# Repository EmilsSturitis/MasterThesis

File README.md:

# MasterThesis
repo with all of the source files

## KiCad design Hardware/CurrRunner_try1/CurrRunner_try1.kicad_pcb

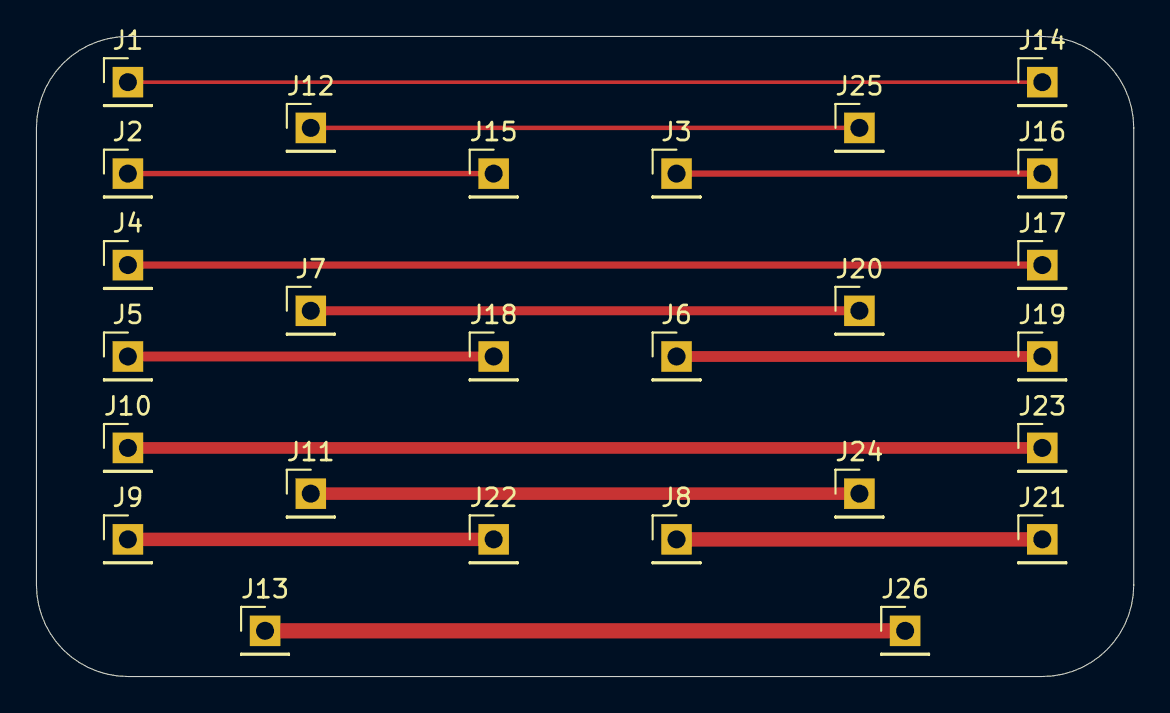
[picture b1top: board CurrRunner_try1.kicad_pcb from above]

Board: 2 copper layers, 61.0 x 35.6 mm, 26 parts (0 on the bottom side), 13 nets.

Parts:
J1, J2, J3, J4, J5, J6, J7, J8, J9, J10, J11, J12, J13, J14, J15, J16, J17, J18, J19, J20, J21, J22, J23, J24, J25, J26: Conn_01x01; PinHeader_1x01_P2.54mm_Vertical

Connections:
unnamed: J1.1, J14.1
unnamed: J10.1, J23.1
unnamed: J11.1, J24.1
unnamed: J12.1, J25.1
unnamed: J13.1, J26.1
unnamed: J2.1, J15.1
unnamed: J3.1, J16.1
unnamed: J4.1, J17.1
unnamed: J5.1, J18.1
unnamed: J6.1, J19.1
unnamed: J7.1, J20.1
unnamed: J8.1, J21.1
unnamed: J9.1, J22.1

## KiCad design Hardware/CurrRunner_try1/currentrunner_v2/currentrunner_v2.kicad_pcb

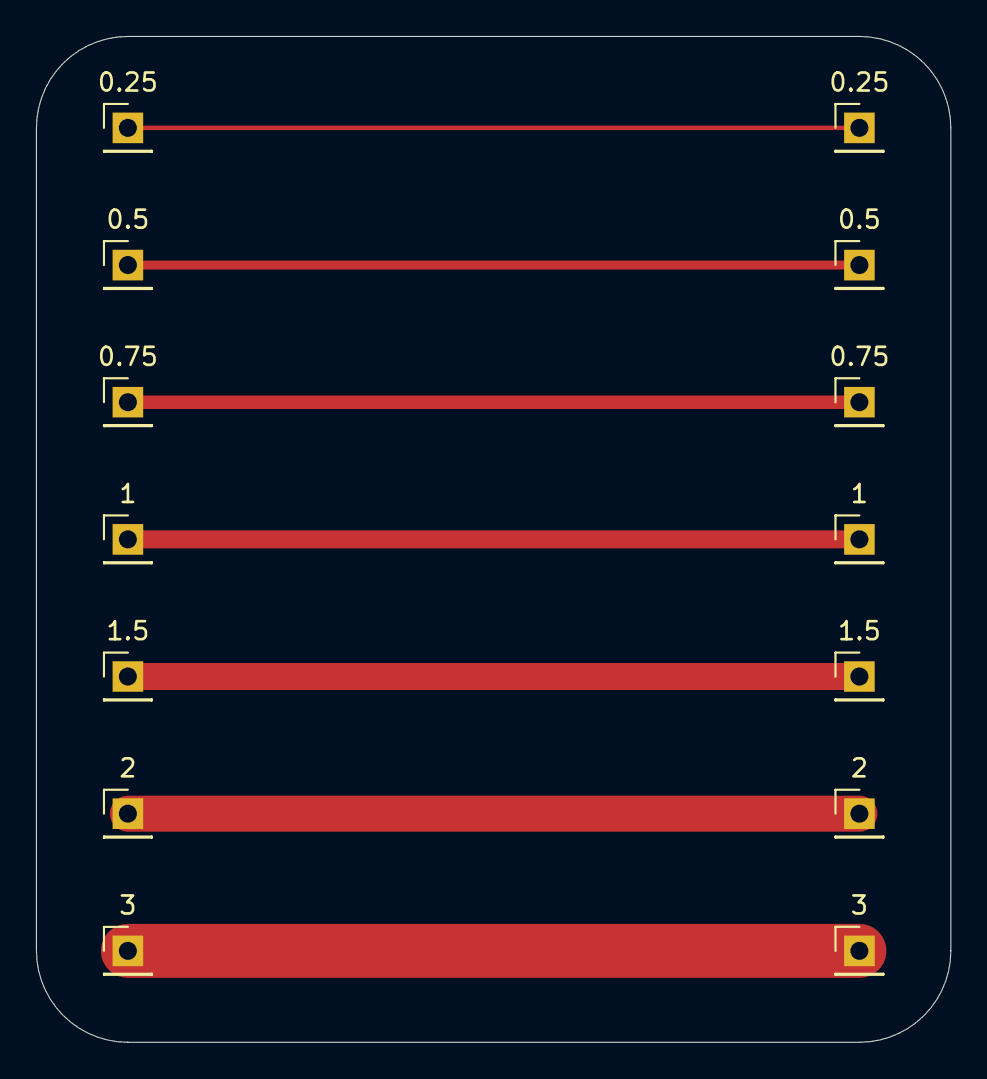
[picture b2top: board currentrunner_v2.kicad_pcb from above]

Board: 2 copper layers, 50.8 x 55.9 mm, 14 parts (0 on the bottom side), 7 nets.

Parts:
J1, J2, J3, J4, J5, J6, J7, J8, J9, J10, J11, J12, J13, J14: Conn_01x01; PinHeader_1x01_P2.54mm_Vertical

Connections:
unnamed: J1.1, J8.1
unnamed: J2.1, J9.1
unnamed: J3.1, J10.1
unnamed: J4.1, J11.1
unnamed: J5.1, J12.1
unnamed: J6.1, J13.1
unnamed: J7.1, J14.1

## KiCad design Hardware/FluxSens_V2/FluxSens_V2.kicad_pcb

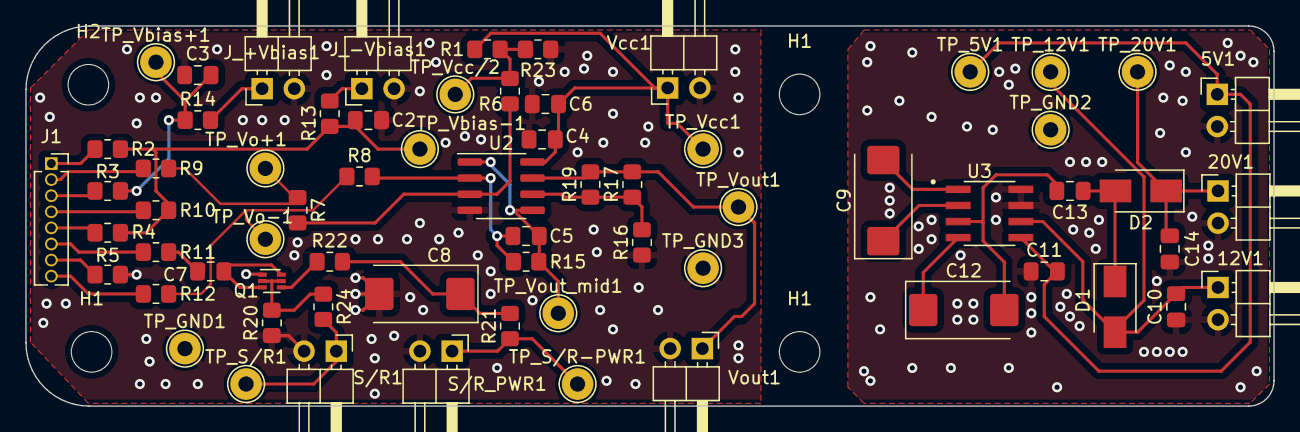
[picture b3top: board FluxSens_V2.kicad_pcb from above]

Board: 2 copper layers, 98.5 x 30.0 mm, 71 parts (0 on the bottom side), 38 nets.

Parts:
5V1, 12V1, 20V1: Conn_01x02; PinHeader_1x02_P2.54mm_Horizontal
C2, C3, C4: 1uF; C_0805_2012Metric_Pad1.18x1.45mm_HandSolder
C5, C10, C13, C14: 100nF; C_0805_2012Metric_Pad1.18x1.45mm_HandSolder
C6, C7: 0.1uF; C_0805_2012Metric_Pad1.18x1.45mm_HandSolder
C8, C9, C12: C_Polarized_Small; CP_EIA-7343-31_Kemet-D_Pad2.25x2.55mm_HandSolder
C11: 2uf; C_0805_2012Metric_Pad1.18x1.45mm_HandSolder
D1, D2: 1N5818; D_SMA
H1, H1#2, H1#3, H2: MountingHole; MountingHole_3.2mm_M3
J1: Conn_01x08; PinSocket_1x08_P1.27mm_Vertical
J_+Vbias1: Conn_01x02; PinHeader_1x02_P2.54mm_Horizontal
J_-Vbias1: Conn_01x02; PinHeader_1x02_P2.54mm_Horizontal
Q1: BSD235C; SOT-563
R1, R23: 10k; R_0805_2012Metric_Pad1.20x1.40mm_HandSolder
R2, R3, R4, R5, R9, R10, R11, R12, R22, R24: 0R; R_0805_2012Metric_Pad1.20x1.40mm_HandSolder
R6, R15: 500k; R_0805_2012Metric_Pad1.20x1.40mm_HandSolder
R7, R8: 5k; R_0805_2012Metric_Pad1.20x1.40mm_HandSolder
R13, R14: 4R; R_0805_2012Metric_Pad1.20x1.40mm_HandSolder
R16: Rb; R_0805_2012Metric_Pad1.20x1.40mm_HandSolder
R17: Ra; R_0805_2012Metric_Pad1.20x1.40mm_HandSolder
R19: Rth; R_0805_2012Metric_Pad1.20x1.40mm_HandSolder
R20: 4k7; R_0805_2012Metric_Pad1.20x1.40mm_HandSolder
R21: 180R; R_0805_2012Metric_Pad1.20x1.40mm_HandSolder
S/R1: Conn_01x02; PinHeader_1x02_P2.54mm_Horizontal
S/R_PWR1: Conn_01x02; PinHeader_1x02_P2.54mm_Horizontal
TP_5V1, TP_12V1, TP_20V1: TestPoint; TestPoint_THTPad_D2.5mm_Drill1.2mm
TP_GND1, TP_GND2, TP_GND3: TestPoint; TestPoint_THTPad_D2.5mm_Drill1.2mm
TP_S/R1: TestPoint; TestPoint_THTPad_D2.5mm_Drill1.2mm
TP_S/R-PWR1: TestPoint; TestPoint_THTPad_D2.5mm_Drill1.2mm
TP_Vbias+1: TestPoint; TestPoint_THTPad_D2.5mm_Drill1.2mm
TP_Vbias-1: TestPoint; TestPoint_THTPad_D2.5mm_Drill1.2mm
TP_Vcc1: TestPoint; TestPoint_THTPad_D2.5mm_Drill1.2mm
TP_Vcc/2: TestPoint; TestPoint_THTPad_D2.5mm_Drill1.2mm
TP_Vo+1: TestPoint; TestPoint_THTPad_D2.5mm_Drill1.2mm
TP_Vo-1: TestPoint; TestPoint_THTPad_D2.5mm_Drill1.2mm
TP_Vout1: TestPoint; TestPoint_THTPad_D2.5mm_Drill1.2mm
TP_Vout_mid1: TestPoint; TestPoint_THTPad_D2.5mm_Drill1.2mm
U2: RC4558; SOIC-8_3.9x4.9mm_P1.27mm
U3: MAX662ACSA+; SOIC127P600X175-8N
Vcc1: Conn_01x02; PinHeader_1x02_P2.54mm_Horizontal
Vout1: Conn_01x02; PinHeader_1x02_P2.54mm_Horizontal

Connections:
/5V: 5V1.1, C11.2, TP_5V1.1, U3.5 (VCC)
/20V: 20V1.1, C14.2, D2.1 (K), TP_20V1.1
/+12V: 12V1.1, C10.2, D1.2 (A), TP_12V1.1, U3.6 (VOUT)
/+Vbias: C3.2, R3.2, R14.1, TP_Vbias+1.1
/-Vbias: C2.2, R2.2, R4.2, R10.2, R13.1, TP_Vbias-1.1
/S/R: Q1.2 (GN), Q1.5 (GP), R20.2, R24.1
/S/R+: C7.1, R11.2
/Vcc: C4.2, C6.2, R1.2, TP_Vcc1.1, U2.8 (V+), Vcc1.1
/Vcc/2: R1.1, R6.1, R23.2, TP_Vcc/2.1
/Vo: R17.2, R19.2, TP_Vout1.1, U2.7, Vout1.1
/Vo+: R7.1, R9.2, TP_Vo+1.1
/Vo-: R8.1, R12.2, TP_Vo-1.1
GND: C2.1, C3.1, C4.1, C6.1, C8.2, J_+Vbias1.2, J_-Vbias1.2, Q1.1 (SN), R5.2, R16.1, R20.1, R23.1, S/R1.2, S/R_PWR1.2, TP_GND1.1, TP_GND3.1, U2.4 (V-), Vcc1.2, Vout1.2
GND2: 5V1.2, 12V1.2, 20V1.2, C10.1, C11.1, C14.1, TP_GND2.1, U3.7 (GND), U3.8 (SHDN)
unnamed: C5.1, R8.2, R15.1, U2.2 (-)
unnamed: C5.2, R15.2, TP_Vout_mid1.1, U2.1, U2.5 (+)
unnamed: C7.2, Q1.3 (DP), Q1.6 (DN)
unnamed: C8.1, R21.2, R22.2
unnamed: C9.1, U3.2 (C1+)
unnamed: C9.2, U3.1 (C1-)
unnamed: C12.1, U3.4 (C2+)
unnamed: C12.2, C13.2, U3.3 (C2-)
unnamed: C13.1, D1.1 (K), D2.2 (A)
unnamed: J1.1, R2.1
unnamed: J1.2, R9.1
unnamed: J1.3, R3.1
unnamed: J1.4, R10.1
unnamed: J1.5, R4.1
unnamed: J1.6, R11.1
unnamed: J1.7, R5.1
unnamed: J1.8, R12.1
unnamed: J_+Vbias1.1, R14.2
unnamed: J_-Vbias1.1, R13.2
unnamed: Q1.4 (SP), R22.1
unnamed: R6.2, R7.2, U2.3 (+)
unnamed: R16.2, R17.1, R19.1, U2.6 (-)
unnamed: R21.1, S/R_PWR1.1, TP_S/R-PWR1.1
unnamed: R24.2, S/R1.1, TP_S/R1.1

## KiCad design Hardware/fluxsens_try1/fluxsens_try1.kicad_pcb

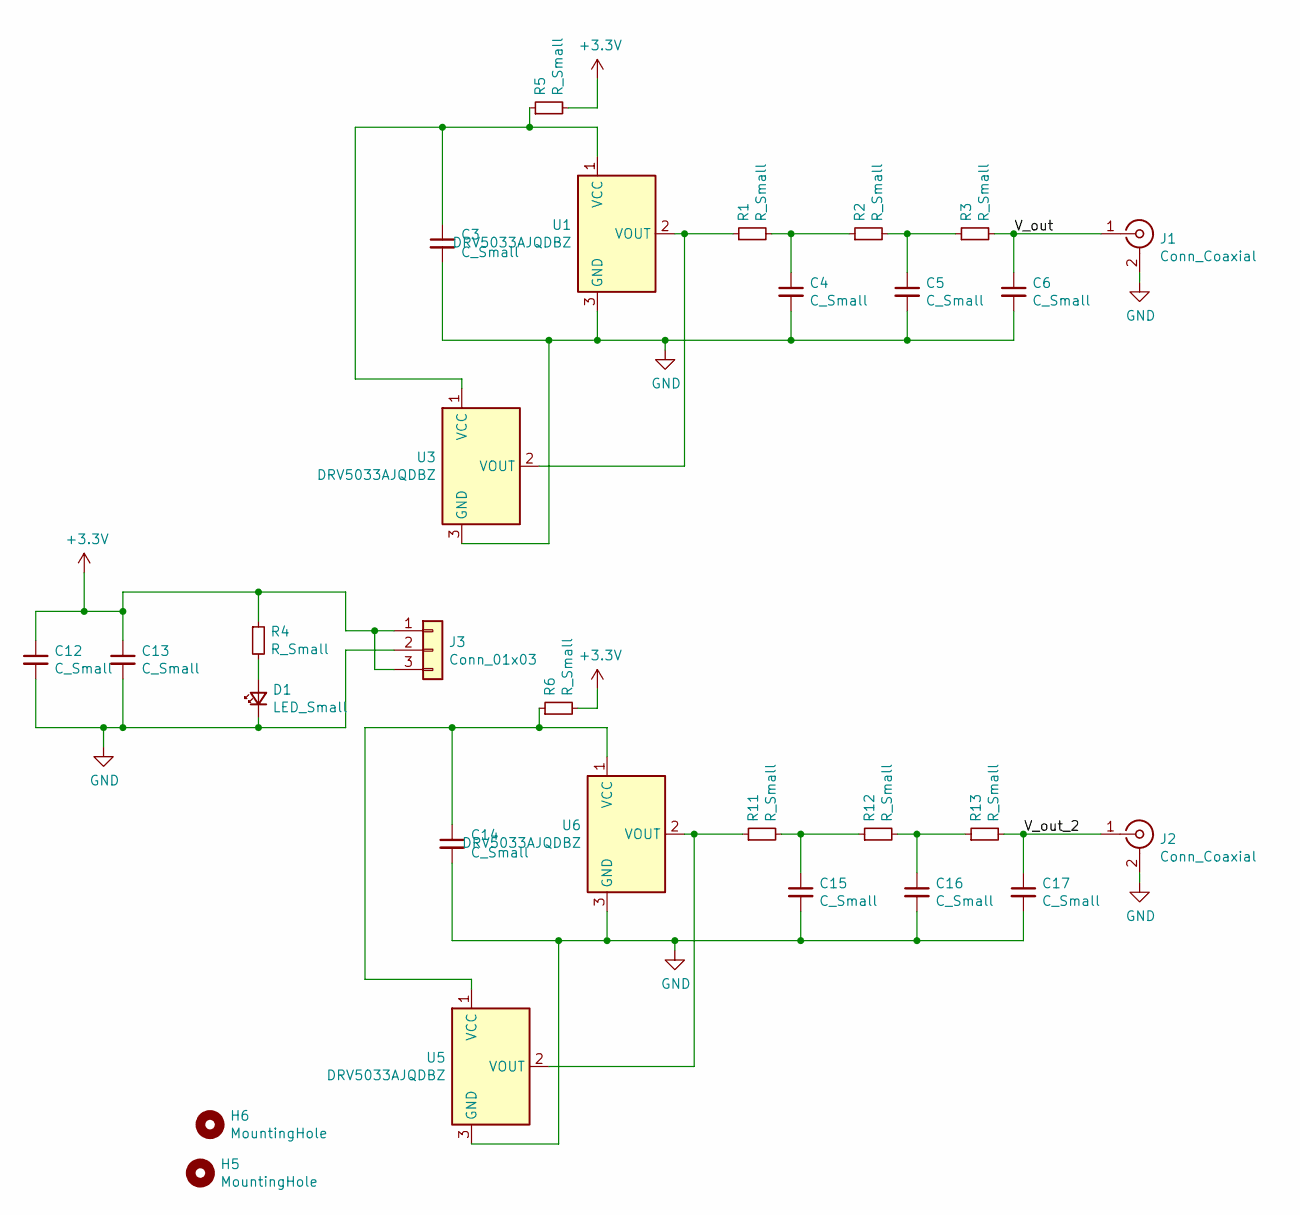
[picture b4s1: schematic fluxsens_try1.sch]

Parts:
C3, C4, C5, C6, C12, C13, C14, C15, C16, C17: C_Small; C_0805_2012Metric_Pad1.18x1.45mm_HandSolder
D1: LED_Small; LED_PLCC-2
H5, H6: MountingHole; MountingHole_3.2mm_M3_DIN965
J1, J2: Conn_Coaxial; SMA_Molex_73251-2120_EdgeMount_Horizontal
J3: Conn_01x03; PinHeader_1x03_P2.54mm_Vertical
R1, R2, R3, R4, R5, R6, R11, R12, R13: R_Small; R_0805_2012Metric_Pad1.20x1.40mm_HandSolder
U1, U3, U5, U6: DRV5033AJQDBZ; SOT-23

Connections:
+3V3: C12.1, C13.1, J3.1, J3.3, R4.1, R5.2, R6.2
/V_out: C6.1, J1.1 (In), R3.2
/V_out_2: C17.1, J2.1 (In), R13.2
GND: C3.2, C4.2, C5.2, C6.2, C12.2, C13.2, C14.2, C15.2, C16.2, C17.2, D1.1 (K), J1.2 (Ext), J2.2 (Ext), J3.2, U1.3 (GND), U3.3 (GND), U5.3 (GND), U6.3 (GND)
unnamed: C3.1, R5.1, U1.1 (VCC), U3.1 (VCC)
unnamed: C4.1, R1.2, R2.1
unnamed: C5.1, R2.2, R3.1
unnamed: C14.1, R6.1, U5.1 (VCC), U6.1 (VCC)
unnamed: C15.1, R11.2, R12.1
unnamed: C16.1, R12.2, R13.1
unnamed: D1.2 (A), R4.2
unnamed: R1.1, U1.2 (VOUT), U3.2 (VOUT)
unnamed: R11.1, U5.2 (VOUT), U6.2 (VOUT)

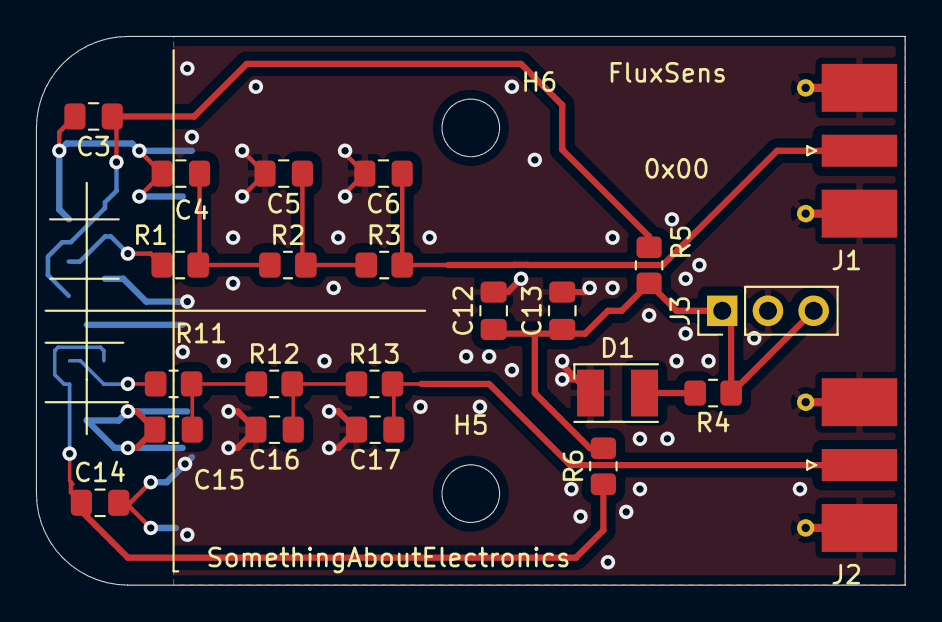
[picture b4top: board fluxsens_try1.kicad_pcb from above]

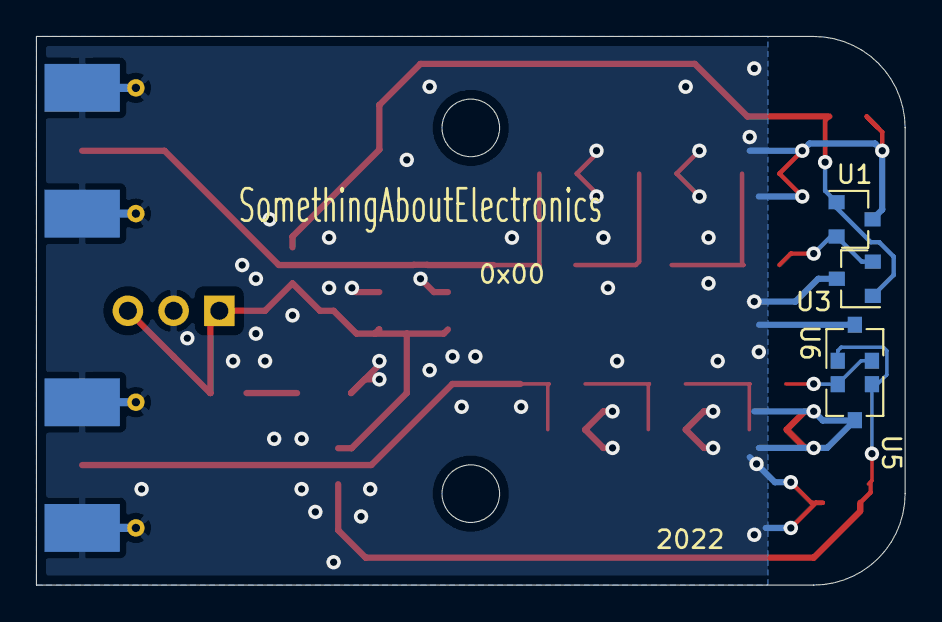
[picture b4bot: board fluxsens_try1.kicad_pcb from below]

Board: 2 copper layers, 48.3 x 30.5 mm, 29 parts (4 on the bottom side), 13 nets.

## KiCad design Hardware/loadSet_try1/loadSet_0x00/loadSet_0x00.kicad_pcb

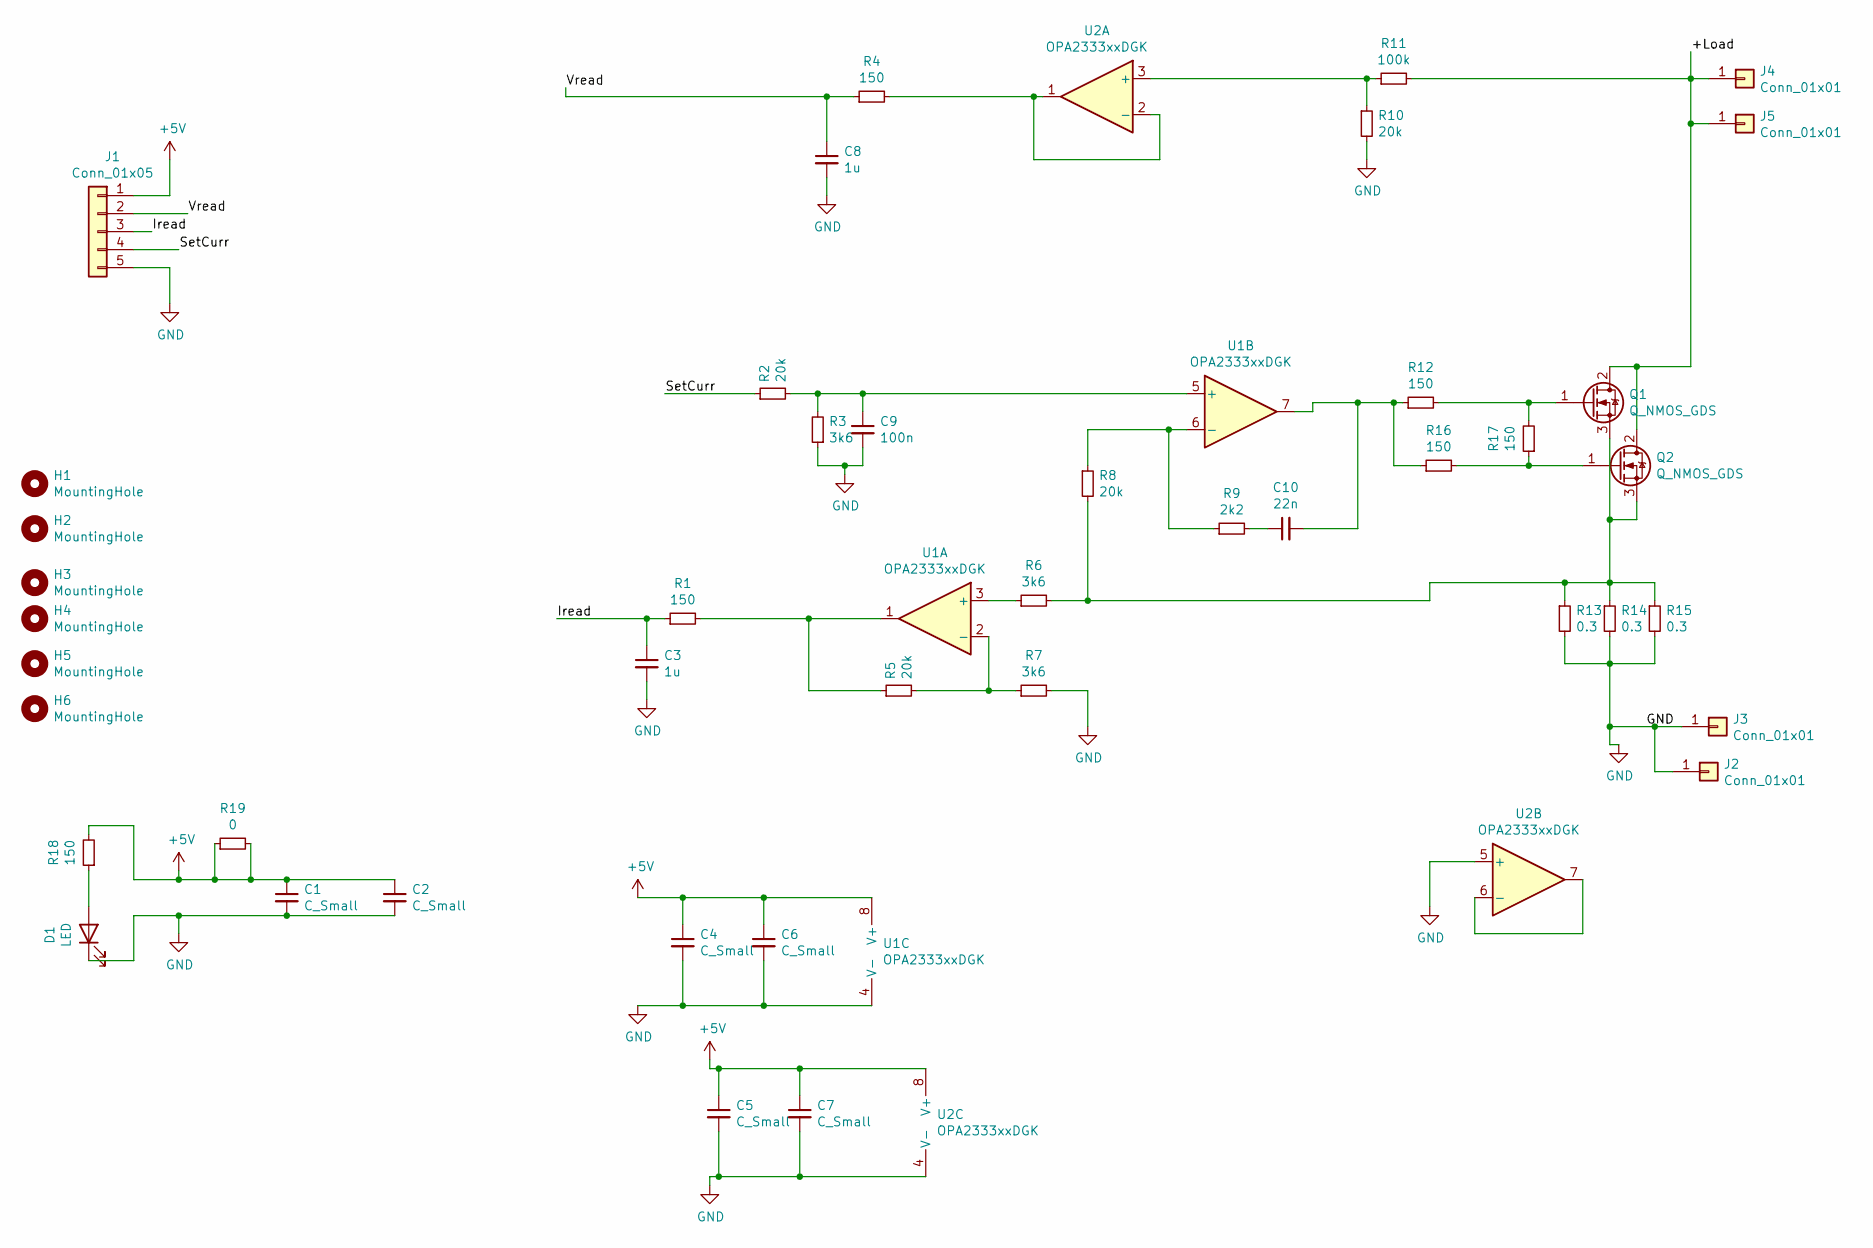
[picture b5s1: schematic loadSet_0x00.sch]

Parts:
C1, C2, C4, C5, C6, C7: C_Small; C_0805_2012Metric_Pad1.18x1.45mm_HandSolder
C3, C8: 1u; C_0805_2012Metric_Pad1.18x1.45mm_HandSolder
C9: 100n; C_0805_2012Metric_Pad1.18x1.45mm_HandSolder
C10: 22n; C_0805_2012Metric_Pad1.18x1.45mm_HandSolder
D1: LED; LED_PLCC-2
H1, H2, H3, H4, H5, H6: MountingHole; MountingHole_3.2mm_M3
J1: Conn_01x05; JST_XH_B5B-XH-AM_1x05_P2.50mm_Vertical
J2, J3, J4, J5: Conn_01x01; Banana_Jack_1Pin
Q1, Q2: Q_NMOS_GDS; TO-220F-3_Vertical
R1, R4, R12, R16, R17, R18: 150; R_0805_2012Metric_Pad1.20x1.40mm_HandSolder
R2, R5, R8, R10: 20k; R_0805_2012Metric_Pad1.20x1.40mm_HandSolder
R3, R6, R7: 3k6; R_0805_2012Metric_Pad1.20x1.40mm_HandSolder
R9: 2k2; R_0805_2012Metric_Pad1.20x1.40mm_HandSolder
R11: 100k; R_0805_2012Metric_Pad1.20x1.40mm_HandSolder
R13, R14, R15: 0.3; R_2512_6332Metric_Pad1.40x3.35mm_HandSolder
R19: 0; R_0805_2012Metric_Pad1.20x1.40mm_HandSolder
U1, U2: OPA2333xxDGK; VSSOP-8_3.0x3.0mm_P0.65mm

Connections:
+5V: C1.1, C2.1, C4.1, C5.1, C6.1, C7.1, J1.1, R18.2, R19.1, R19.2, U1.8 (V+), U2.8 (V+)
/+Load: J4.1, J5.1, Q1.2 (D), Q2.2 (D), R11.2
/Iread: C3.1, J1.3, R1.1
/SetCurr: J1.4, R2.1
/Vread: C8.1, J1.2, R4.1
GND: C1.2, C2.2, C3.2, C4.2, C5.2, C6.2, C7.2, C8.2, C9.2, D1.1 (K), J1.5, J2.1, J3.1, R3.1, R7.2, R10.2, R13.2, R14.2, R15.2, U1.4 (V-), U2.4 (V-), U2.5 (+)
unnamed: C9.1, R2.2, R3.2, U1.5 (+)
unnamed: C10.1, R9.2
unnamed: C10.2, R12.1, R16.1, U1.7
unnamed: D1.2 (A), R18.1
unnamed: Q1.1 (G), R12.2, R17.2
unnamed: Q1.3 (S), Q2.3 (S), R6.2, R8.2, R13.1, R14.1, R15.1
unnamed: Q2.1 (G), R16.2, R17.1
unnamed: R1.2, R5.1, U1.1
unnamed: R4.2, U2.1, U2.2 (-)
unnamed: R5.2, R7.1, U1.2 (-)
unnamed: R6.1, U1.3 (+)
unnamed: R8.1, R9.1, U1.6 (-)
unnamed: R10.1, R11.1, U2.3 (+)
unnamed: U2.6 (-), U2.7

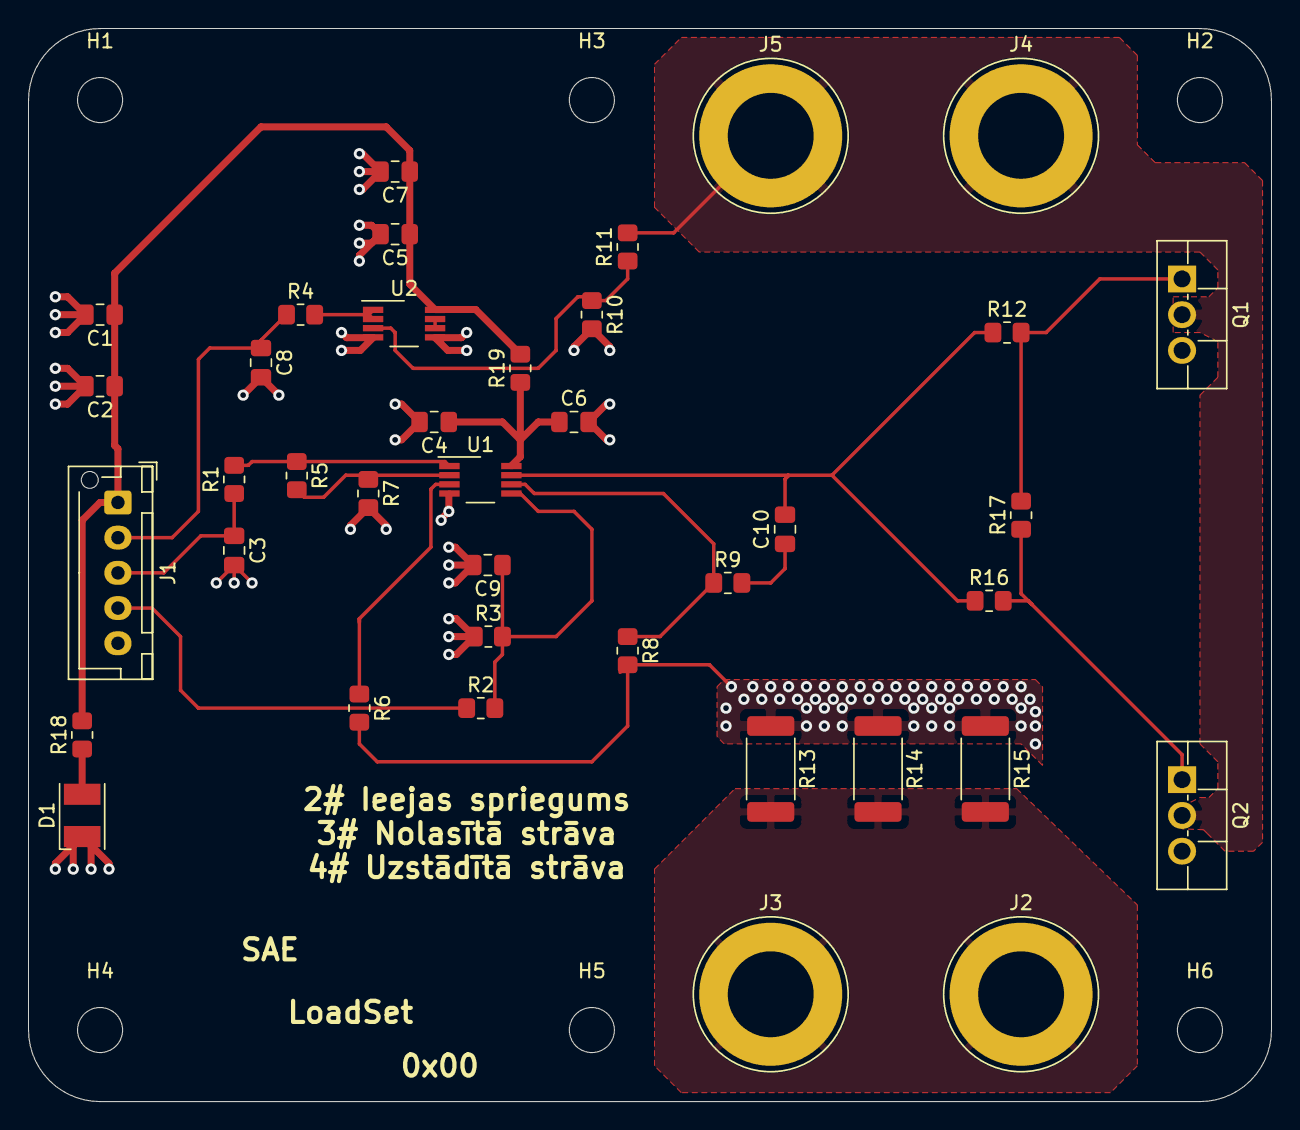
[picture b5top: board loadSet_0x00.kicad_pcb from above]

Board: 2 copper layers, 88.3 x 76.2 mm, 45 parts (0 on the bottom side), 20 nets.

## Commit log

2023-01-09 Initial and only commit
